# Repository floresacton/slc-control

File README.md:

# slc-control
Display Controller for SLC Kit Car

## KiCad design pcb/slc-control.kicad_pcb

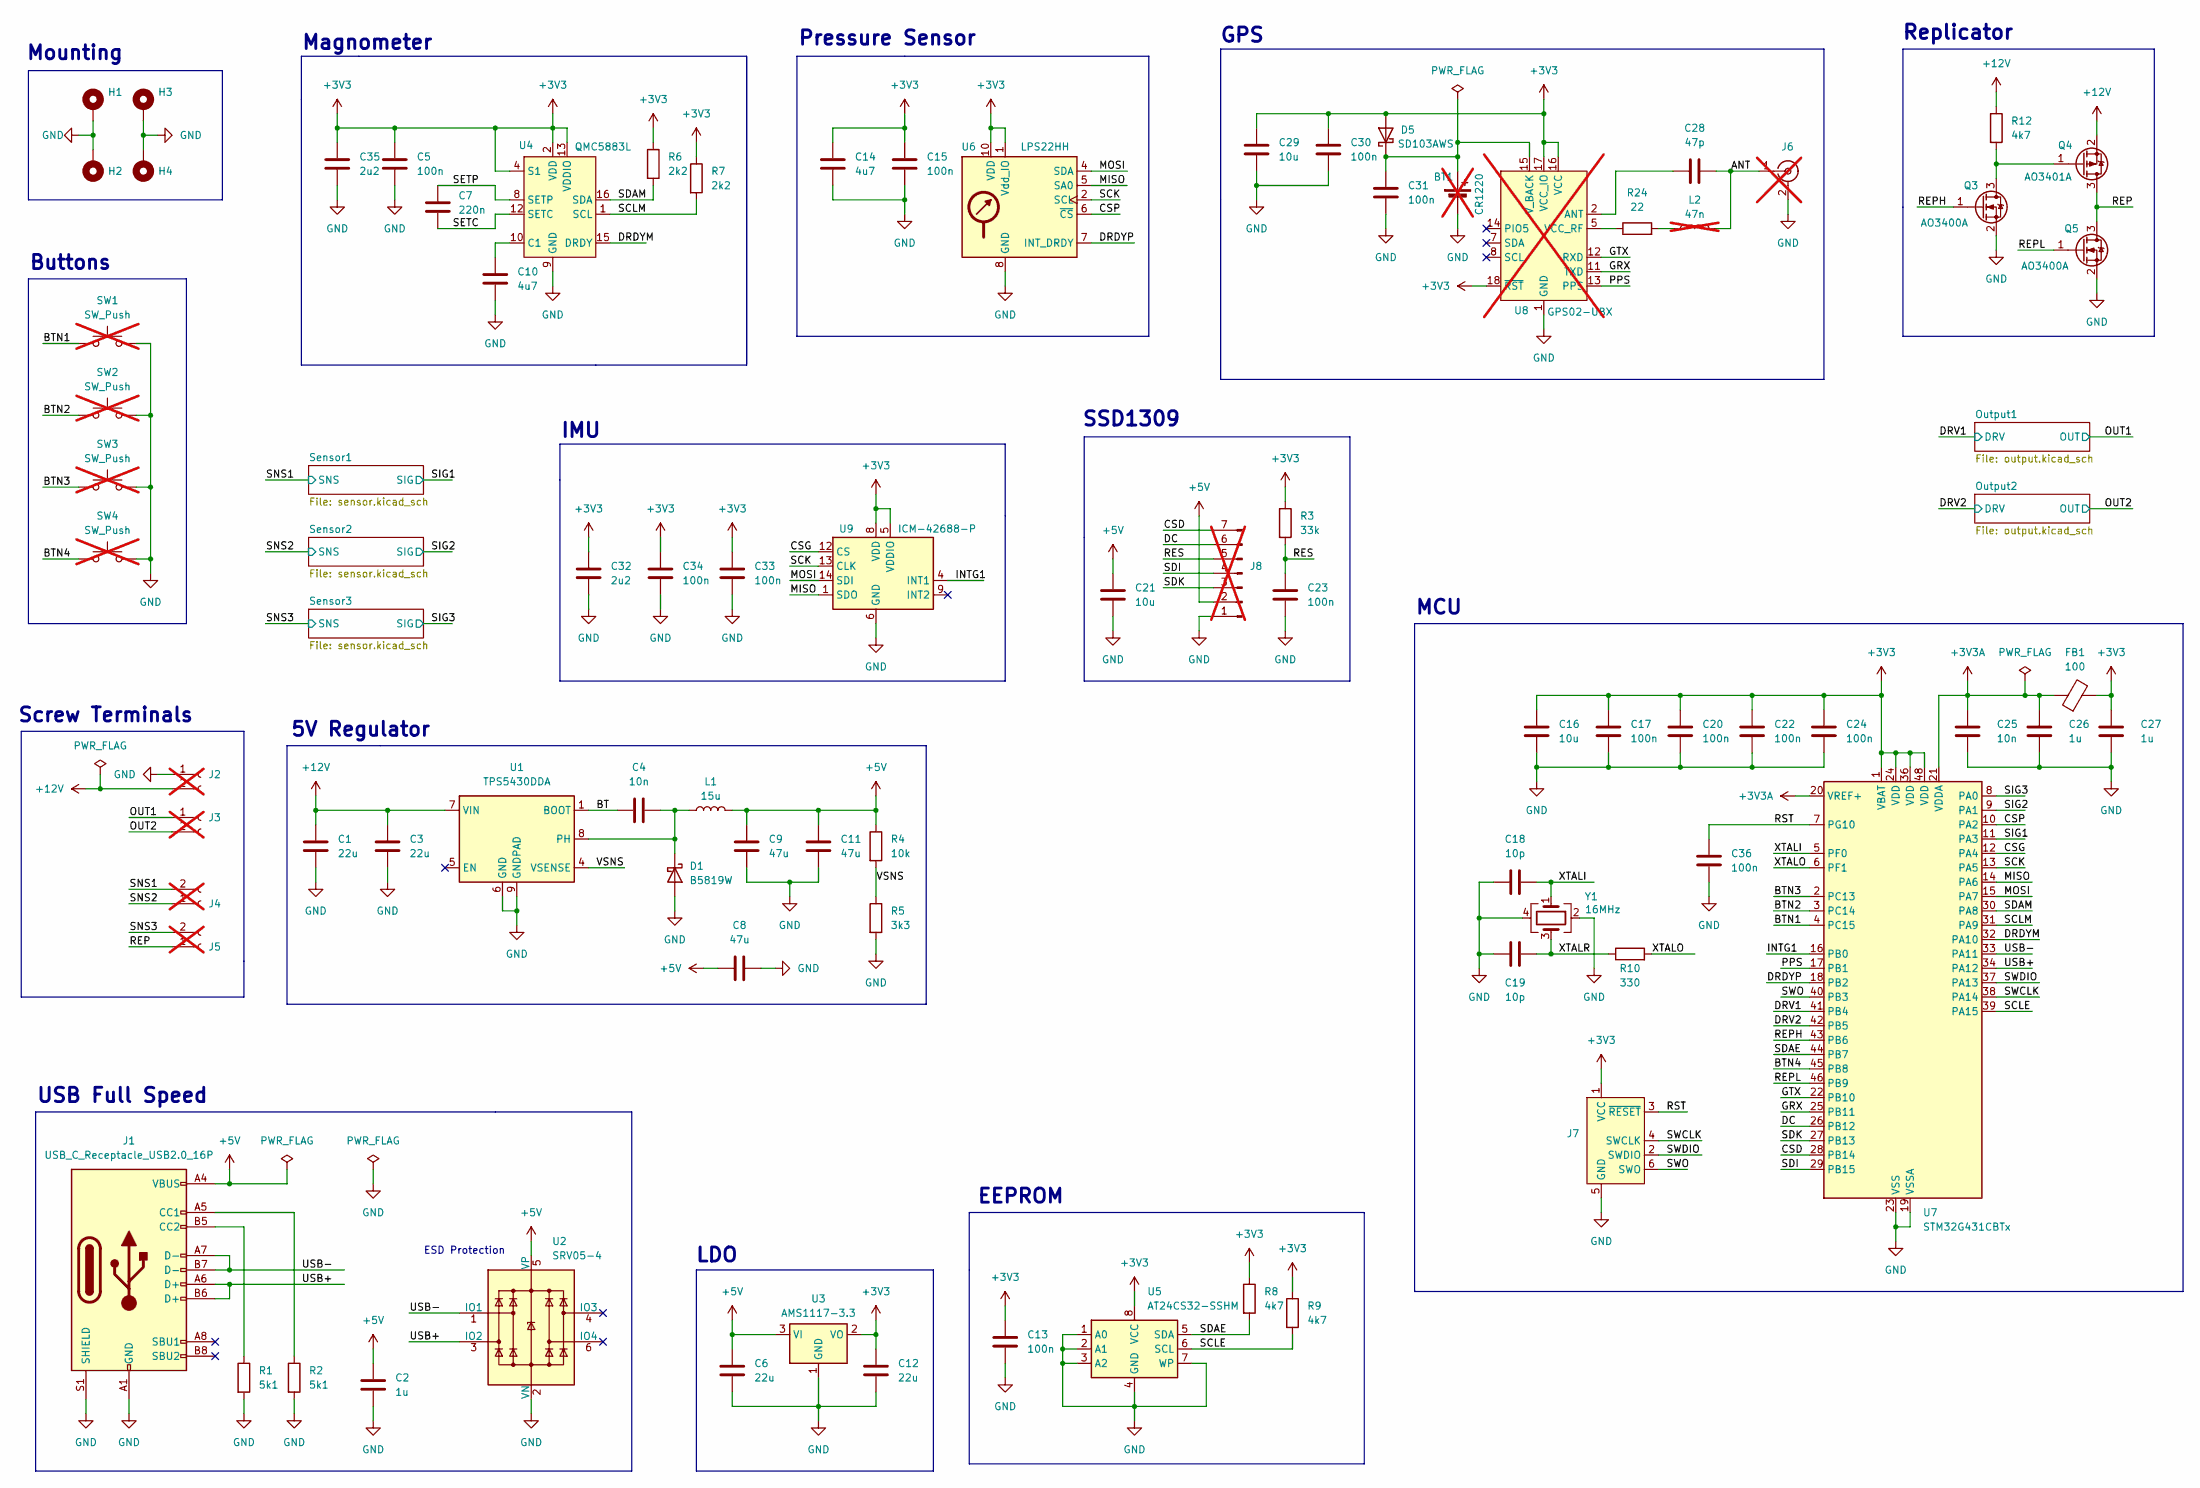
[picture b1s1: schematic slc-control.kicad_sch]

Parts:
BT1: CR1220; LCSC C70381; not fitted
C1, C3: 22u; C_1206_3216Metric; LCSC C12891
C2, C26, C27: 1u; C_0402_1005Metric; LCSC C52923
C4, C25: 10n; C_0402_1005Metric; LCSC C15195
C5, C13, C15, C17, C20, C22, C23, C24, C30, C31, C33, C34, C36: 100n; C_0402_1005Metric; LCSC C1525
C6: 22u; C_0805_2012Metric; LCSC C45783
C7: 220n; C_0402_1005Metric; LCSC C16772
C8, C9, C11: 47u; C_1206_3216Metric; LCSC C96123
C10: 4u7; C_0603_1608Metric; LCSC C19666
C12: 22u; C_0603_1608Metric; LCSC C59461
C14: 4u7; C_0402_1005Metric; LCSC C23733
C16, C21, C29: 10u; C_0603_1608Metric; LCSC C19702
C18, C19: 10p; C_0402_1005Metric; LCSC C32949
C28: 47p; C_0402_1005Metric; LCSC C1567
C32, C35: 2u2; C_0402_1005Metric; LCSC C12530
D1: B5819W; D_SOD-123; LCSC C8598
D5: SD103AWS; D_SOD-323; LCSC C7420360
FB1: 100; L_0805_2012Metric; LCSC C1015
H1, H2, H3, H4: MountingHole_Pad; MountingHole_5.3mm_M5_ISO7380_Pad
J1: USB_C_Receptacle_USB2.0_16P; USB_C_Receptacle_GCT_USB4105-xx-A_16P_TopMnt_Horizontal; LCSC C2765186
J2, J3, J4, J5: Conn_01x02_Socket; WJ126V-5.0-2P; LCSC C8404; not fitted
J6: Conn_Coaxial; BWSMA-KWE-Z001; LCSC C496551; not fitted
J7: Conn_ARM_SWD_TagConnect_TC2030-NL; Tag-Connect_TC2030-IDC-NL_2x03_P1.27mm_Vertical
J8: Conn_01x07_Pin; PinHeader_1x07_P2.54mm_Vertical; not fitted
L1: 15u; L_Changjiang_FNR6020S; LCSC C168015
L2: 47n; L_0603_1608Metric; LCSC C98076; not fitted
Q3, Q5: AO3400A; SOT-23; LCSC C20917
Q4: AO3401A; SOT-23; LCSC C15127
R1, R2: 5k1; R_0402_1005Metric; LCSC C25905
R3: 33k; R_0402_1005Metric; LCSC C25779
R4: 10k; R_0402_1005Metric; LCSC C25744
R5: 3k3; R_0402_1005Metric; LCSC C25890
R6, R7: 2k2; R_0402_1005Metric; LCSC C25879
R8, R9, R12: 4k7; R_0402_1005Metric; LCSC C25900
R10: 330; R_0402_1005Metric; LCSC C25104
R24: 22; R_0402_1005Metric; LCSC C25092
SW1, SW2, SW3, SW4: SW_Push; SW_PUSH_6mm_H9.5mm; LCSC C455119; not fitted
U1: TPS5430DDA; TI_SO-PowerPAD-8_ThermalVias; LCSC C9864
U2: SRV05-4; SOT-23-6; LCSC C7420376
U3: AMS1117-3.3; SOT-223-3_TabPin2; LCSC C6186
U4: QMC5883L; LGA-16_3x3mm_P0.5mm; LCSC C976032
U5: AT24CS32-SSHM; SOIC-8_3.9x4.9mm_P1.27mm; LCSC C6482
U6: LPS22HH; ST_HLGA-10_2x2mm_P0.5mm_LayoutBorder3x2y; LCSC C2827824
U7: STM32G431CBTx; LQFP-48_7x7mm_P0.5mm; LCSC C529355
U8: GPS02-UBX; LCSC C5356636; not fitted
U9: ICM-42688-P; LGA-14_3x2.5mm_P0.5mm_LayoutBorder3x4y; LCSC C1850418
Y1: 16MHz; Crystal_SMD_3225-4Pin_3.2x2.5mm; LCSC C13738

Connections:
+3V3: C5.1, C12.1, C13.1, C14.1, C15.1, C16.1, C17.1, C20.1, C22.1, C24.1, C27.1, C29.1, C30.1, C32.1, C33.1, C34.1, C35.1, D5.2 (A), FB1.2, J7.1 (VCC), R3.1, R6.1, R7.1, R8.1, R9.1, U3.2 (VO), U4.2 (VDD), U4.4 (S1), U4.13 (VDDIO), U5.8 (VCC), U6.1 (Vdd_IO), U6.10 (VDD), U7.1 (VBAT), U7.24 (VDD), U7.36 (VDD), U7.48 (VDD), U8.16 (VCC), U8.17 (VCC_IO), U8.18 (~RST), U9.5 (VDDIO), U9.8 (VDD)
+3V3A: C25.1, C26.1, FB1.1, U7.20 (VREF+), U7.21 (VDDA)
+5V: C2.1, C6.1, C8.1, C9.1, C11.1, C21.1, J1.A4 (VBUS), J1.A9 (VBUS), J1.B4 (VBUS), J1.B9 (VBUS), J8.2, L1.2, R4.1, U2.5 (VP), U3.3 (VI)
+12V: C1.1, C3.1, J2.2, Q4.2 (S), R12.1, U1.7 (VIN); also elsewhere on the board
/ANT: C28.2, J6.1 (In), L2.2
/BT: C4.1, U1.1 (BOOT)
/BTN1: SW1.1, U7.4 (PC15)
/BTN2: SW2.1, U7.3 (PC14)
/BTN3: SW3.1, U7.2 (PC13)
/BTN4: SW4.1, U7.45 (PB8)
/CSD: J8.7, U7.28 (PB14)
/CSG: U7.12 (PA4), U9.12 (CS)
/CSP: U6.6 (~CS), U7.10 (PA2)
/DC: J8.6, U7.26 (PB12)
/DRDYM: U4.15 (DRDY), U7.32 (PA10)
/DRDYP: U6.7 (INT_DRDY), U7.18 (PB2)
/DRV1: U7.41 (PB4); also elsewhere on the board
/DRV2: U7.42 (PB5); also elsewhere on the board
/GRX: U7.25 (PB11), U8.11 (TXD)
/GTX: U7.22 (PB10), U8.12 (RXD)
/INTG1: U7.16 (PB0), U9.4 (INT1)
/MISO: U6.5 (SA0), U7.14 (PA6), U9.1 (SDO)
/MOSI: U6.4 (SDA), U7.15 (PA7), U9.14 (SDI)
/OUT1: J3.1; also elsewhere on the board
/OUT2: J3.2; also elsewhere on the board
/PPS: U7.17 (PB1), U8.13 (PPS)
/REP: J5.1, Q4.3 (D), Q5.3 (D)
/REPH: Q3.1 (G), U7.43 (PB6)
/REPL: Q5.1 (G), U7.46 (PB9)
/RES: C23.1, J8.5, R3.2
/RST: C36.1, J7.3 (~RESET), U7.7 (PG10)
/SCK: U6.2 (SCL), U7.13 (PA5), U9.13 (CLK)
/SCLE: R9.2, U5.6 (SCL), U7.39 (PA15)
/SCLM: R7.2, U4.1 (SCL), U7.31 (PA9)
/SDAE: R8.2, U5.5 (SDA), U7.44 (PB7)
/SDAM: R6.2, U4.16 (SDA), U7.30 (PA8)
/SDI: J8.4, U7.29 (PB15)
/SDK: J8.3, U7.27 (PB13)
/SETC: C7.2, U4.12 (SETC)
/SETP: C7.1, U4.8 (SETP)
/SIG1: U7.11 (PA3); also elsewhere on the board
/SIG2: U7.9 (PA1); also elsewhere on the board
/SIG3: U7.8 (PA0); also elsewhere on the board
/SNS1: J4.2; also elsewhere on the board
/SNS2: J4.1; also elsewhere on the board
/SNS3: J5.2; also elsewhere on the board
/SWCLK: J7.4 (SWCLK), U7.38 (PA14)
/SWDIO: J7.2 (SWDIO), U7.37 (PA13)
/SWO: J7.6 (SWO), U7.40 (PB3)
/USB+: J1.A6 (D+), J1.B6 (D+), U2.3 (IO2), U7.34 (PA12)
/USB-: J1.A7 (D-), J1.B7 (D-), U2.1 (IO1), U7.33 (PA11)
/VSNS: R4.2, R5.1, U1.4 (VSENSE)
/XTALI: C18.2, U7.5 (PF0), Y1.1
/XTALO: R10.2, U7.6 (PF1)
/XTALR: C19.2, R10.1, Y1.3
GND: BT1.2 (-), C1.2, C2.2, C3.2, C5.2, C6.2, C8.2, C9.2, C10.2, C11.2, C12.2, C13.2, C14.2, C15.2, C16.2, C17.2, C18.1, C19.1, C20.2, C21.2, C22.2, C23.2, C24.2, C25.2, C26.2, C27.2, C29.2, C30.2, C31.2, C32.2, C33.2, C34.2, C35.2, C36.2, D1.2 (A), H1.1, H2.1, H3.1, H4.1, J1.A1 (GND), J1.A12 (GND), J1.B1 (GND), J1.B12 (GND), J1.S1 (SHIELD), J2.1, J6.2 (Ext), J7.5 (GND), J8.1, Q3.2 (S), Q5.2 (S), R1.2, R2.2, R5.2, SW1.2, SW2.2, SW3.2, SW4.2, U1.6 (GND), U1.9 (GNDPAD), U2.2 (VN), U3.1 (GND), U4.9 (GND), U4.11 (GND), U5.1 (A0), U5.2 (A1), U5.3 (A2), U5.4 (GND), U5.7 (WP), U6.3 (GND), U6.8 (GND), U6.9 (GND), U7.19 (VSSA), U7.23 (VSS), U7.35 (VSS), U7.47 (VSS), U8.1 (GND), U8.3 (GND), U8.10 (GND), U9.6 (GND), U9.7 (RESV), U9.11 (RESV), Y1.2, Y1.4; also elsewhere on the board
unnamed: BT1.1 (+), C31.1, D5.1 (K), U8.15 (V_BACK)
unnamed: C4.2, D1.1 (K), L1.1, U1.8 (PH)
unnamed: J1.A5 (CC1), R2.1
unnamed: J1.B5 (CC2), R1.1
unnamed: L2.1, R24.2
unnamed: Q3.3 (D), Q4.1 (G), R12.2
unnamed: C10.1, U4.10 (C1)
unnamed: C28.1, U8.2 (ANT)
unnamed: R24.1, U8.5 (VCC_RF)

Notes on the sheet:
5V Regulator
Mounting
USB Full Speed
Buttons
Magnometer
Screw Terminals
ESD Protection
GPS
SSD1309
Pressure Sensor
IMU
Replicator
LDO
MCU
EEPROM

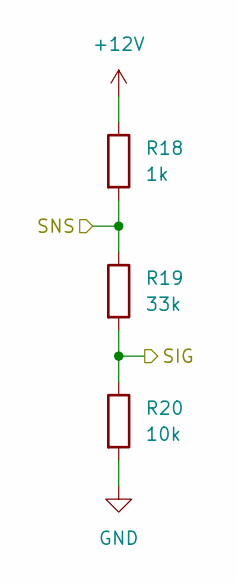
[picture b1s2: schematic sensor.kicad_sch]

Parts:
R18: 1k; R_1206_3216Metric; LCSC C4410
R19: 33k; R_0402_1005Metric; LCSC C25779
R20: 10k; R_0402_1005Metric; LCSC C25744

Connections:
+12V: R18.1; also elsewhere on the board
/SIG2: R19.2, R20.1; also elsewhere on the board
/SNS2: R18.2, R19.1; also elsewhere on the board
GND: R20.2; also elsewhere on the board

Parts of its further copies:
R15, R21: 1k; R_1206_3216Metric; LCSC C4410
R16, R22: 33k; R_0402_1005Metric; LCSC C25779
R17, R23: 10k; R_0402_1005Metric; LCSC C25744

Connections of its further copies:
+12V: R15.1, R21.1; also elsewhere on the board
/SIG1: R16.2, R17.1; also elsewhere on the board
/SIG3: R22.2, R23.1; also elsewhere on the board
/SNS1: R15.2, R16.1; also elsewhere on the board
/SNS3: R21.2, R22.1; also elsewhere on the board
GND: R17.2, R23.2; also elsewhere on the board

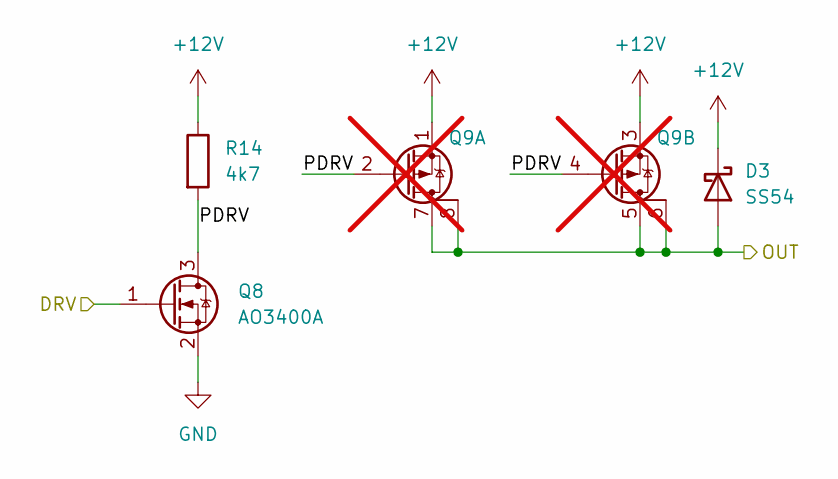
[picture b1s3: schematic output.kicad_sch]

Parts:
D3: SS54; D_SMA; LCSC C22452
Q8: AO3400A; SOT-23; LCSC C20917
Q9: Q_Dual_PMOS_S1G1S2G2D2D2D1D1; SO-8_3.9x4.9mm_P1.27mm; LCSC C725015; not fitted
R14: 4k7; R_0402_1005Metric; LCSC C25900

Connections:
+12V: D3.1 (K), Q9.1 (S), Q9.3 (S), R14.1; also elsewhere on the board
/DRV2: Q8.1 (G); also elsewhere on the board
/OUT2: D3.2 (A), Q9.5 (D), Q9.6 (D), Q9.7 (D), Q9.8 (D); also elsewhere on the board
/Output2/PDRV: Q8.3 (D), Q9.2 (G), Q9.4 (G), R14.2
GND: Q8.2 (S); also elsewhere on the board

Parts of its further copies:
D2: SS54; D_SMA; LCSC C22452
Q6: AO3400A; SOT-23; LCSC C20917
Q7: Q_Dual_PMOS_S1G1S2G2D2D2D1D1; SO-8_3.9x4.9mm_P1.27mm; LCSC C725015; not fitted
R13: 4k7; R_0402_1005Metric; LCSC C25900

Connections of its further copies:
+12V: D2.1 (K), Q7.1 (S), Q7.3 (S), R13.1; also elsewhere on the board
/DRV1: Q6.1 (G); also elsewhere on the board
/OUT1: D2.2 (A), Q7.5 (D), Q7.6 (D), Q7.7 (D), Q7.8 (D); also elsewhere on the board
/Output1/PDRV: Q6.3 (D), Q7.2 (G), Q7.4 (G), R13.2
GND: Q6.2 (S); also elsewhere on the board

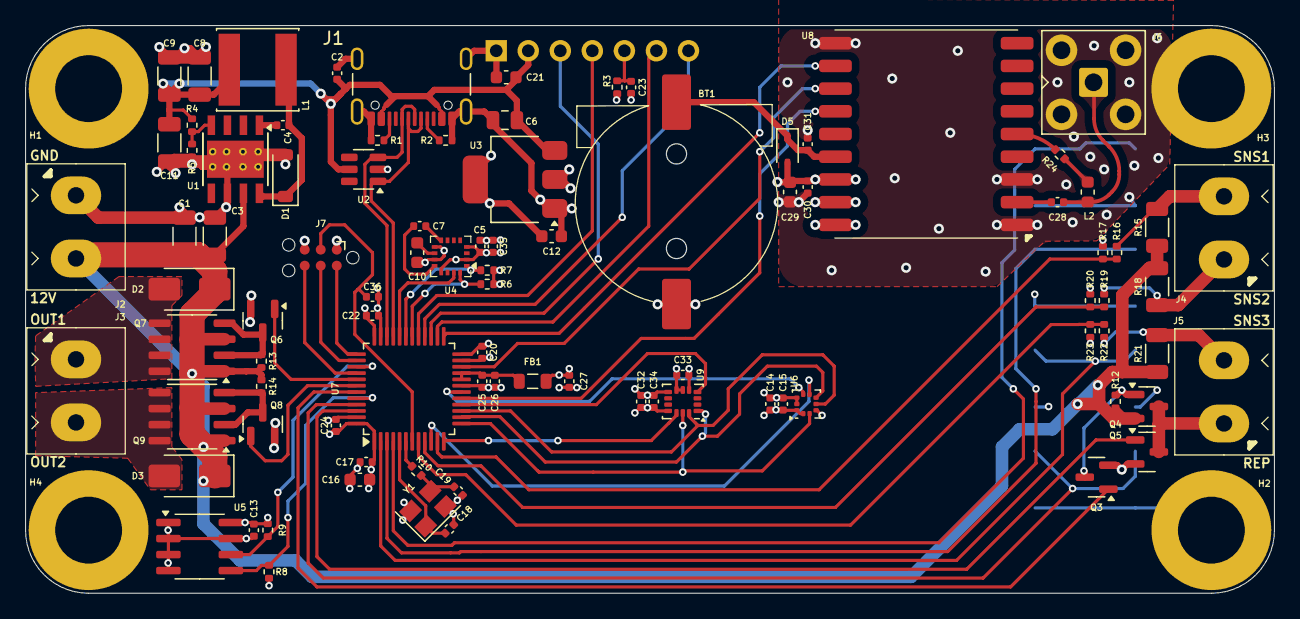
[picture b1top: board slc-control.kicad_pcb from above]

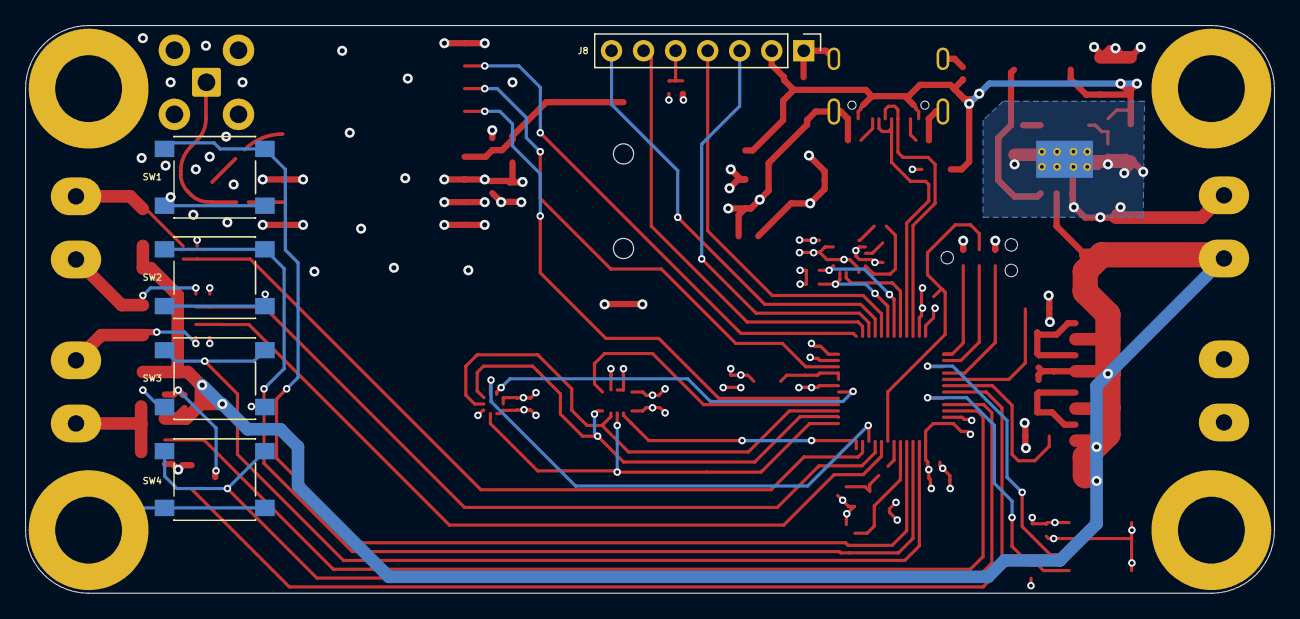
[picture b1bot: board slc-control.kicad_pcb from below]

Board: 4 copper layers, 99.0 x 45.0 mm, 100 parts (5 on the bottom side), 67 nets.

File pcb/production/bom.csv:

Designator,Footprint,Quantity,Value,LCSC Part #
"C1, C3",1206,2,22u,C12891
C10,0603,1,4u7,C19666
"C11, C8, C9",1206,3,47u,C96123
C12,0603,1,22u,C59461
"C13, C15, C17, C20, C22, C23, C24, C30, C31, C33, C34, C36, C5",0402,13,100n,C1525
C14,0402,1,4u7,C23733
"C16, C21, C29",0603,3,10u,C19702
"C18, C19",0402,2,10p,C32949
"C2, C26, C27",0402,3,1u,C52923
"C25, C4",0402,2,10n,C15195
C28,0402,1,47p,C1567
"C32, C35",0402,2,2u2,C12530
C6,0805,1,22u,C45783
C7,0402,1,220n,C16772
D1,D_SOD-123,1,B5819W,C8598
"D2, D3",D_SMA,2,SS54,C22452
D5,D_SOD-323,1,SD103AWS,C7420360
FB1,0805,1,100,C1015
J1,USB_C_Receptacle_GCT_USB4105-xx-A_16P_TopMnt_Horizontal,1,USB_C_Receptacle_USB2.0_16P,C2765186
L1,L_Changjiang_FNR6020S,1,15u,C168015
"Q3, Q5, Q6, Q8",SOT-23,4,AO3400A,C20917
Q4,SOT-23,1,AO3401A,C15127
"R1, R2",0402,2,5k1,C25905
R10,0402,1,330,C25104
"R12, R13, R14, R8, R9",0402,5,4k7,C25900
"R15, R18, R21",1206,3,1k,C4410
"R16, R19, R22, R3",0402,4,33k,C25779
"R17, R20, R23, R4",0402,4,10k,C25744
R24,0402,1,22,C25092
R5,0402,1,3k3,C25890
"R6, R7",0402,2,2k2,C25879
U1,TI_SO-PowerPAD-8_ThermalVias,1,TPS5430DDA,C9864
U2,SOT-23-6,1,SRV05-4,C7420376
U3,SOT-223-3_TabPin2,1,AMS1117-3.3,C6186
U4,LGA-16_3x3mm_P0.5mm,1,QMC5883L,
U5,SOIC-8_3.9x4.9mm_P1.27mm,1,AT24CS32-SSHM,C6482
U6,ST_HLGA-10_2x2mm_P0.5mm_LayoutBorder3x2y,1,LPS22HH,C2827824
U7,LQFP-48_7x7mm_P0.5mm,1,STM32G431CBTx,C529355
U9,LGA-14_3x2.5mm_P0.5mm_LayoutBorder3x4y,1,ICM-42688-P,C1850418
Y1,Crystal_SMD_3225-4Pin_3.2x2.5mm,1,16MHz,C13738

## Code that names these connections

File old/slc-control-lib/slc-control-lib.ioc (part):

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Mcu.Name=STM32G431C(6-8-B)Tx
Mcu.Package=LQFP48
Mcu.UserName=STM32G431CBTx
PA0.GPIOParameters=GPIO_Label
PA0.GPIO_Label=SIG3
PA0.Mode=INP
PA0.Signal=COMP3_INP
PA1.GPIOParameters=GPIO_Label
PA1.GPIO_Label=SIG2
PA1.Mode=INP
PA1.Signal=COMP1_INP
PA10.GPIOParameters=GPIO_Label,GPIO_ModeDefaultEXTI
PA10.GPIO_Label=DRDYM
PA10.GPIO_ModeDefaultEXTI=GPIO_MODE_IT_RISING
PA10.Signal=GPXTI10
PA11.Mode=Device
PA11.Signal=USB_DM
PA12.Mode=Device
PA12.Signal=USB_DP
PA13.Mode=Trace_Asynchronous_SW
PA13.Signal=SYS_JTMS-SWDIO
PA14.Mode=Trace_Asynchronous_SW
PA14.Signal=SYS_JTCK-SWCLK
PA15.GPIOParameters=GPIO_Speed,GPIO_Label
PA15.GPIO_Label=SCLE
PA15.GPIO_Speed=GPIO_SPEED_FREQ_MEDIUM
PA15.Mode=I2C
PA15.Signal=I2C1_SCL
PA2.GPIOParameters=GPIO_Speed,PinState,GPIO_Label
PA2.GPIO_Label=CSP
PA2.GPIO_Speed=GPIO_SPEED_FREQ_HIGH
PA2.PinState=GPIO_PIN_SET
PA2.Signal=GPIO_Output
PA3.GPIOParameters=GPIO_Label
PA3.GPIO_Label=SIG1
PA3.Mode=INP
PA3.Signal=COMP2_INP
PA4.GPIOParameters=GPIO_Speed,PinState,GPIO_Label
PA4.GPIO_Label=CSG
PA4.GPIO_Speed=GPIO_SPEED_FREQ_HIGH
PA4.PinState=GPIO_PIN_SET
PA4.Signal=GPIO_Output
PA5.GPIOParameters=GPIO_Label
PA5.GPIO_Label=SCKM
PA5.Mode=Full_Duplex_Master
PA5.Signal=SPI1_SCK
PA6.GPIOParameters=GPIO_Label
PA6.GPIO_Label=MISOM
PA6.Mode=Full_Duplex_Master
PA6.Signal=SPI1_MISO
PA7.GPIOParameters=GPIO_Label
PA7.GPIO_Label=MOSIM
PA7.Mode=Full_Duplex_Master
PA7.Signal=SPI1_MOSI
PA8.GPIOParameters=GPIO_Speed,GPIO_Label
PA8.GPIO_Label=SDAM
PA8.GPIO_Speed=GPIO_SPEED_FREQ_MEDIUM
PA8.Mode=I2C
PA8.Signal=I2C2_SDA
PA9.GPIOParameters=GPIO_Speed,GPIO_Label
PA9.GPIO_Label=SCLM
PA9.GPIO_Speed=GPIO_SPEED_FREQ_MEDIUM
PA9.Mode=I2C
PA9.Signal=I2C2_SCL
PB0.GPIOParameters=GPIO_Label
PB0.GPIO_Label=INTG
PB0.Signal=GPXTI0
PB1.GPIOParameters=GPIO_Label
PB1.GPIO_Label=PPS
PB1.Signal=GPXTI1
PB10.GPIOParameters=GPIO_Label
PB10.GPIO_Label=GTX
PB10.Mode=Asynchronous
PB10.Signal=USART3_TX
PB11.GPIOParameters=GPIO_Label
PB11.GPIO_Label=GRX
PB11.Mode=Asynchronous
PB11.Signal=USART3_RX
PB12.GPIOParameters=GPIO_Speed,GPIO_Label
PB12.GPIO_Label=DC
PB12.GPIO_Speed=GPIO_SPEED_FREQ_HIGH
PB12.Signal=GPIO_Output
PB13.GPIOParameters=GPIO_Speed,GPIO_Label
PB13.GPIO_Label=SCKD
PB13.GPIO_Speed=GPIO_SPEED_FREQ_HIGH
PB13.Mode=TX_Only_Simplex_Unidirect_Master
PB13.Signal=SPI2_SCK
PB14.GPIOParameters=GPIO_Speed,PinState,GPIO_Label
PB14.GPIO_Label=CSD
PB14.GPIO_Speed=GPIO_SPEED_FREQ_HIGH
PB14.PinState=GPIO_PIN_SET
PB14.Signal=GPIO_Output
PB15.GPIOParameters=GPIO_Speed,GPIO_Label
PB15.GPIO_Label=MOSID
PB15.GPIO_Speed=GPIO_SPEED_FREQ_HIGH
PB15.Mode=TX_Only_Simplex_Unidirect_Master
PB15.Signal=SPI2_MOSI
PB2.GPIOParameters=GPIO_Label
PB2.GPIO_Label=DRDYP
PB2.Signal=GPXTI2
PB3.Mode=Trace_Asynchronous_SW
PB3.Signal=SYS_JTDO-SWO
PB4.GPIOParameters=GPIO_Speed,GPIO_Label
PB4.GPIO_Label=DRV1
PB4.GPIO_Speed=GPIO_SPEED_FREQ_MEDIUM
PB4.Signal=GPIO_Output
PB5.GPIOParameters=GPIO_Speed,GPIO_Label
PB5.GPIO_Label=DRV2
PB5.GPIO_Speed=GPIO_SPEED_FREQ_MEDIUM
PB5.Signal=GPIO_Output
PB6.GPIOParameters=GPIO_Label
PB6.GPIO_Label=REPH
PB6.Signal=GPIO_Output
PB7.GPIOParameters=GPIO_Speed,GPIO_Label
PB7.GPIO_Label=SDAE
PB7.GPIO_Speed=GPIO_SPEED_FREQ_MEDIUM
PB7.Mode=I2C
PB7.Signal=I2C1_SDA
PB8-BOOT0.GPIOParameters=GPIO_PuPd,GPIO_Label
PB8-BOOT0.GPIO_Label=BTN4
PB8-BOOT0.GPIO_PuPd=GPIO_PULLUP
PB8-BOOT0.Signal=GPIO_Input
PB9.GPIOParameters=GPIO_Label
PB9.GPIO_Label=REPL
PB9.Signal=GPIO_Output
PC13.GPIOParameters=GPIO_PuPd,GPIO_Label
PC13.GPIO_Label=BTN3
PC13.GPIO_PuPd=GPIO_PULLUP
PC13.Signal=GPIO_Input
PC14-OSC32_IN.GPIOParameters=GPIO_PuPd,GPIO_Label
PC14-OSC32_IN.GPIO_Label=BTN2
PC14-OSC32_IN.GPIO_PuPd=GPIO_PULLUP
PC14-OSC32_IN.Signal=GPIO_Input
PC15-OSC32_OUT.GPIOParameters=GPIO_PuPd,GPIO_Label
PC15-OSC32_OUT.GPIO_Label=BTN1
PC15-OSC32_OUT.GPIO_PuPd=GPIO_PULLUP
PC15-OSC32_OUT.Signal=GPIO_Input
PF0-OSC_IN.Mode=HSE-External-Oscillator
PF0-OSC_IN.Signal=RCC_OSC_IN
PF1-OSC_OUT.Mode=HSE-External-Oscillator
PF1-OSC_OUT.Signal=RCC_OSC_OUT
RCC.HSE_VALUE=16000000
RCC.SYSCLKFreq_VALUE=144000000
RCC.SYSCLKSource=RCC_SYSCLKSOURCE_PLLCLK
board=custom

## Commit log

2025-01-04 Configure project
2025-01-04 Setup stmlib
2025-01-05 Update fimware from old project
2025-01-24 Save
2025-07-25 Setup display
2025-07-26 Fix magnometer and pressure
2025-07-30 Update tach
2025-07-31 Test tachometer
2025-08-01 Bring in stm-lib dependencies
2025-08-02 Update gps and menus
2025-08-03 Add replicator feature
2025-08-04 Finish replicator
2025-08-06 Finish accelerometer
2025-08-06 Finish home screen
2025-08-06 Fix gps interrupt issues
2025-08-06 Fix bugs
2025-08-06 Fix oled font scaling
2025-08-19 Fix gps text and accels
2025-08-27 Add minor fixes
2025-09-28 Add images
